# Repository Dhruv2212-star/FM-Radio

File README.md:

# Dhruv's FM-Radio 
A simple FM radio that can search for channels and connect to them with the given controls from 87-108 MHz that can fit in your palms !  

## Virtual Controls for our radio-  
1.  s = seek up  
2.  S = seek down  
3. "+" = tune +100 kHz  
4.  "-" = tune -100 kHz  
5.  V = increase RDA5807 digital volume  
6.  v = decrease RDA5807 digital volume  
7.  m = mute/unmute  
8.  i = print radio status

**PCB Dimentions- 40mm x 55mm x 1.6 mm**  

# How to use the final Radio?
To use the final radio, connect the microcontroller to your laptop/desktop and flash the firmware on and it'll show a new panel, you can use the above keys for the controls  

## Case
our case is made into 2 parts, the Bottom case and the Top case, the top case will snugly fit on the bottom case because of it's low tolerance 

**Top Case**  

**Bottom Case** 

# Final Assembly 
what our final product will look like (ignore the empty spaces, its for speakers) 

## PCB

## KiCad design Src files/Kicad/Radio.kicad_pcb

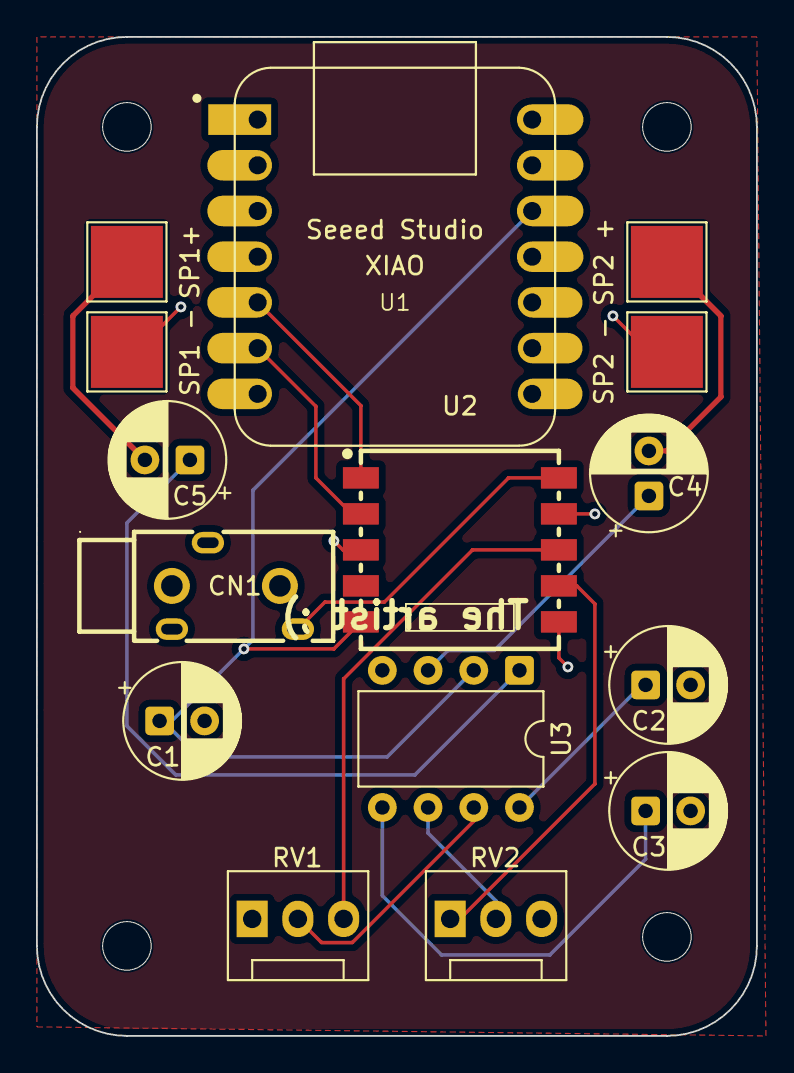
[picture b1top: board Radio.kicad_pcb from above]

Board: 2 copper layers, 40.0 x 55.5 mm, 19 parts (0 on the bottom side), 15 nets.

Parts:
C1, C2, C3, C4, C5: 100uF; CP_Radial_D6.3mm_P2.50mm
CN1: PJ-3200; AUDIO-TH_PJ-3200
H1, H2, H3, H4: MountingHole; MountingHole_2.7mm_M2.5
RV1, RV2: 10K; FanPinHeader_1x03_P2.54mm_Vertical
SP1 -: SP -; TestPoint_Pad_4.0x4.0mm
SP1+: SP1 +; TestPoint_Pad_4.0x4.0mm
SP2 +: SP2 +; TestPoint_Pad_4.0x4.0mm
SP2 -: SP2 -; TestPoint_Pad_4.0x4.0mm
U1: MOUDLE-SEEEDUINO-XIAO; XIAO-Generic-Hybrid-14P-2.54-21X17.8MM
U2: RDA5807MRRD-102V2.0; RDA5807
U3: TDA2822NBD; DIP-8_W7.62mm

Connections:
+3V3: C1.1, U1.12 (3V3), U2.5 (VCC), U3.2 (VCC)
/L-OUT: RV2.1, U2.7 (L-OUT)
/R-OUT: RV1.3, U2.8 (R-OUT)
GND: C1.2, C2.2, C3.2, CN1.3, RV1.1, RV2.3, SP1 -.1 (1_1), SP2 -.1 (1_1), U1.13 (GND), U2.3 (GND), U2.6 (GND), U2.9 (GND), U3.4 (GND)
unnamed: C4.2, SP2 +.1 (1_1)
unnamed: C5.2, SP1+.1 (1_1)
unnamed: U1.5 (PA8_A4_D4_SDA), U2.1 (DATA)
unnamed: U1.6 (PA9_A5_D5_SCL), U2.2 (CLK)
unnamed: CN1.4, U2.10 (ANT)
unnamed: RV1.2, U3.7 (IN1)
unnamed: RV2.2, U3.6 (IN2)
unnamed: C2.1, U3.8 (NF1)
unnamed: C3.1, U3.5 (NF2)
unnamed: C5.1, U3.1 (OUT1)
unnamed: C4.1, U3.3 (OUT2)

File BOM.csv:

Ref,Value,Description,Qty,KiCad Symbol,Footprint,India seller,Unit cost (INR),Buy / product page
U1,MOUDLE-SEEEDUINO-XIAO,Seeed Studio XIAO RP2040,1,XIAO_RP2040:MOUDLE-SEEEDUINO-XIAO,my footprints:XIAO-Generic-Hybrid-14P-2.54-21X17.8MM,Robocraze,?589,https://robocraze.com/pages/seeed-studio
U2,RDA5807MRRD-102V2.0,RDA5807M RRD-102 V2.0 FM module,1,Static_Symbol_Library:RDA5807MRRD-102V2.0,Static:RDA5807,ElectronicsComp,?67.26,https://www.electronicscomp.com/rda5807m-fm-stereo-radio-mod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
U3,TDA2822NBD,"TDA2822 dual audio amplifier, DIP-8",1,Static_Symbol_Library:TDA2822NBD,Package_DIP:DIP-8_W7.62mm,Robu.in (equivalent TDA2822M),?9,https://robu.in/product-category/electronic-components/integ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
RV1,10K,WH148 10K potentiometer,1,Device:R_Potentiometer,Connector:FanPinHeader_1x03_P2.54mm_Vertical,AM Electronics India,?12,https://amelectronics.in/product/10k-potentiometer/
RV2,10K,WH148 10K potentiometer,1,Device:R_Potentiometer,Connector:FanPinHeader_1x03_P2.54mm_Vertical,AM Electronics India,?12,https://amelectronics.in/product/10k-potentiometer/
C1,100uF,100 µF polarized electrolytic capacitor,1,Device:C_Polarized,Capacitor_THT:CP_Radial_D6.3mm_P2.50mm,ElectronicsComp,??3.74,https://www.electronicscomp.com/100uf-16v-electrolytic-capacitor
C2,100uF,100 µF polarized electrolytic capacitor,1,Device:C_Polarized,Capacitor_THT:CP_Radial_D6.3mm_P2.50mm,ElectronicsComp,??3.74,https://www.electronicscomp.com/100uf-16v-electrolytic-capacitor
C3,100uF,100 µF polarized electrolytic capacitor,1,Device:C_Polarized,Capacitor_THT:CP_Radial_D6.3mm_P2.50mm,ElectronicsComp,??3.74,https://www.electronicscomp.com/100uf-16v-electrolytic-capacitor
C4,100uF,100 µF polarized electrolytic capacitor,1,Device:C_Polarized,Capacitor_THT:CP_Radial_D6.3mm_P2.50mm,ElectronicsComp,??3.74,https://www.electronicscomp.com/100uf-16v-electrolytic-capacitor
C5,100uF,100 µF polarized electrolytic capacitor,1,Device:C_Polarized,Capacitor_THT:CP_Radial_D6.3mm_P2.50mm,ElectronicsComp,??3.74,https://www.electronicscomp.com/100uf-16v-electrolytic-capacitor
CN1,PJ-3200,"3.5 mm stereo audio jack, PJ-3200",1,Static_Symbol_Library:PJ-3200,Static:AUDIO-TH_PJ-3200,Evelta,?4.72,https://evelta.com/3-5mm-female-audio-jack-connector-3pin-1/
TP1,SP1 +,"SMD solder pad, 4x4 mm",1,Connector:TestPoint,TestPoint:TestPoint_Pad_4.0x4.0mm,,,https://kicad.github.io/footprints/TestPoint.html
TP2,SP -,"SMD solder pad, 4x4 mm",1,Connector:TestPoint,TestPoint:TestPoint_Pad_4.0x4.0mm,,,https://kicad.github.io/footprints/TestPoint.html
TP3,SP2 +,"SMD solder pad, 4x4 mm",1,Connector:TestPoint,TestPoint:TestPoint_Pad_4.0x4.0mm,,,https://kicad.github.io/footprints/TestPoint.html
TP4,SP2 -,"SMD solder pad, 4x4 mm",1,Connector:TestPoint,TestPoint:TestPoint_Pad_4.0x4.0mm,,,https://kicad.github.io/footprints/TestPoint.html
